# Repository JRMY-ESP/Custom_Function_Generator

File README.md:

# Custom_Function_Generator
This project implements a basic analog function generator that can produce a square, triangle, and sine wave for general purposes.  This design is implemented in three main stages. For the first stage, the design implements an op amp in the configuration of an oscillator to generate a square wave. This square is then driven into the next two stages which are integrators that convert the square wave into triangle, and sine waves.

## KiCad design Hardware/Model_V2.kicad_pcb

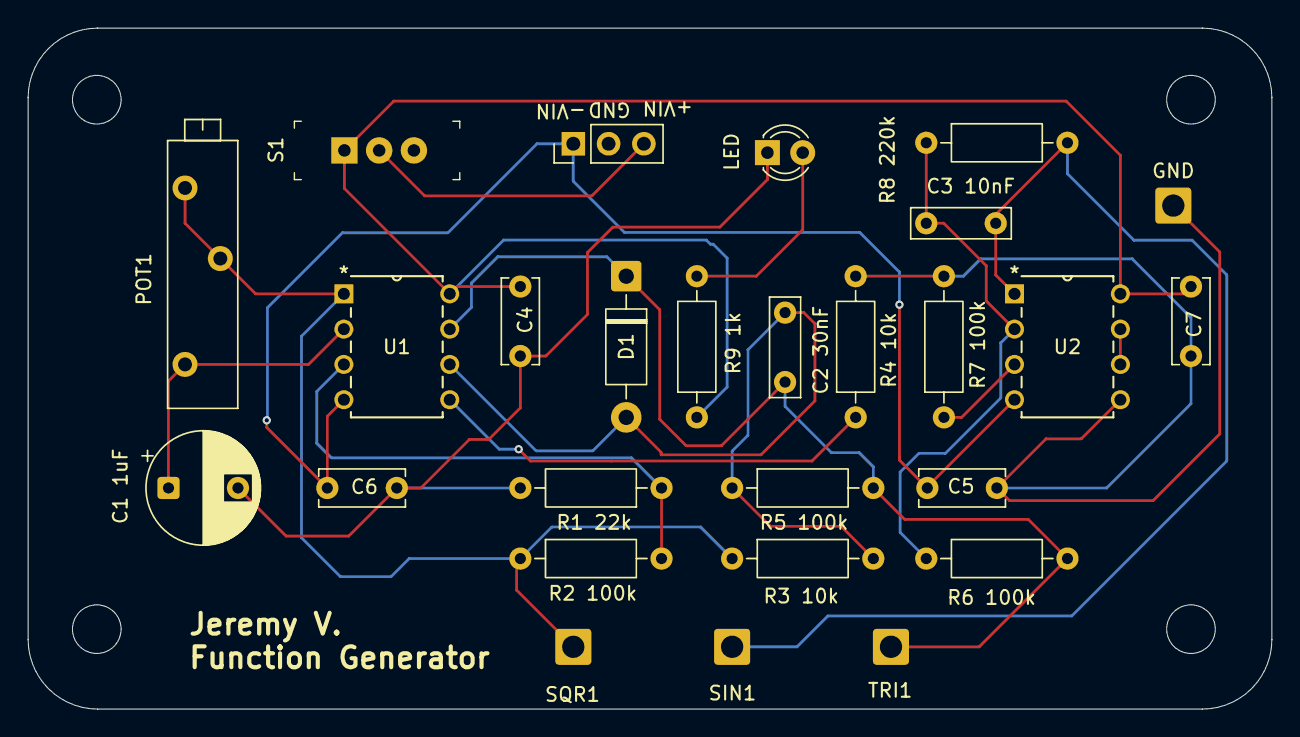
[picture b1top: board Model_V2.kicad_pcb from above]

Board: 2 copper layers, 89.5 x 49.0 mm, 27 parts (0 on the bottom side), 15 nets.

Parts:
C1 1uF: 1uF; CP_Radial_D8.0mm_P5.00mm
C2 30nF: 30nF; C_Rect_L7.0mm_W2.0mm_P5.00mm
C3 10nF: 10nF; C_Rect_L7.0mm_W2.0mm_P5.00mm
C4, C5, C6, C7: C; C_Disc_D6.0mm_W2.5mm_P5.00mm
D1: 1N4001; D_DO-41_SOD81_P10.16mm_Horizontal
GND: Conn_01x01; SolderWire-0.75sqmm_1x01_D1.25mm_OD2.3mm
J1: Conn_01x03; PinHeader_1x03_P2.54mm_Vertical
LED: LED; LED_D3.0mm
POT1: TC33X-2-103E; Potentiometer_Bourns_3006P_Horizontal
R1 22k: 22k; R_Axial_DIN0207_L6.3mm_D2.5mm_P10.16mm_Horizontal
R2 100k, R5 100k, R6 100k, R7 100k: 100k; R_Axial_DIN0207_L6.3mm_D2.5mm_P10.16mm_Horizontal
R3 10k, R4 10k: 10k; R_Axial_DIN0207_L6.3mm_D2.5mm_P10.16mm_Horizontal
R8 220k: 220k; R_Axial_DIN0207_L6.3mm_D2.5mm_P10.16mm_Horizontal
R9 1k: 1k; R_Axial_DIN0207_L6.3mm_D2.5mm_P10.16mm_Horizontal
S1: EG1218; Switch_Slide_11.6x4mm_EG1218
SIN1: Conn_01x01; SolderWire-0.75sqmm_1x01_D1.25mm_OD2.3mm
SQR1: Conn_01x01; SolderWire-0.75sqmm_1x01_D1.25mm_OD2.3mm
TRI1: Conn_01x01; SolderWire-0.75sqmm_1x01_D1.25mm_OD2.3mm
U1, U2: NE5532_P_8; NE5532P

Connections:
+VIN: C4.1, C7.1, R9 1k.1, S1.1, U1.8 (VCC+), U2.8 (VCC+)
-VIN: C5.1, C6.1, J1.1, U1.4 (VCC-), U2.4 (VCC-)
GND: C1 1uF.2, C4.2, C5.2, C6.2, C7.2, GND.1, J1.2, LED.1 (K), R1 22k.2, R4 10k.2, R7 100k.2, U2.5 (2IN+)
unnamed: C2 30nF.2, D1.2 (A), R3 10k.2, R5 100k.1, U1.6 (2IN-)
unnamed: C2 30nF.1, D1.1 (K), R5 100k.2, R6 100k.1, TRI1.1, U1.7 (2OUT)
unnamed: LED.2 (A), R9 1k.2
unnamed: J1.3, S1.2
unnamed: C1 1uF.1, POT1.1 (CCW), U1.2 (1IN-)
unnamed: POT1.2 (Wiper), POT1.3 (CW), R2 100k.1, R3 10k.1, SQR1.1, U1.1 (1OUT)
unnamed: C3 10nF.2, R8 220k.2, SIN1.1, U2.1 (1OUT)
unnamed: R1 22k.1, R2 100k.2, U1.3 (1IN+)
unnamed: R4 10k.1, U1.5 (2IN+)
unnamed: R7 100k.1, U2.3 (1IN+)
unnamed: C3 10nF.1, R6 100k.2, R8 220k.1, U2.2 (1IN-)
unnamed: U2.6 (2IN-), U2.7 (2OUT)

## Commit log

2026-04-13 Hardware design files for function generator
    KiCad project, schematic, and PCB layout
2026-04-13 Update README with project description
    Added project description and functionality details.
2026-04-13 Gerber Files for manufacturing
